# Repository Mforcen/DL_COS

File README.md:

# DL_COS
This project aims to develop a proof of concept of a datalogger with a several tasks operating concurrently in a cooperative way.

Although the name is an acronym for Cooperative Operating System, it is not really an Operating System, since it can't stop the execution of a task.

All the modules are programmed following a state machine structure, with functions that won't block, hence the Cooperative part of the name.

The firmware includes several components. Among them, we can find:

1. A simple stack-based bytecode interpreter. This module is important because it offers two enhancements. In one hand it allows the device to execute programs can be load from flash without reprogram the whole OS. On the other hand, the user does not have to take care about the cooperative behaviour, since the execution of the program is controlled by the module. Finally, this makes the communication quite simple, since a user only needs to call the write function and the OS executes the communications asyncronously, halting the execution of the bytecode program until the communication is finished. This module is intended to use with another piece of software.
2. A SDI12 driver. This manages the communications with several field sensors. This module allows the device to read all the data from the sensors, following the SDI12 specification. This piece of software only needs two timers and a GPIO pin with interruptions enabled. This driver is tested with several SDI12 devices, such as MPS6 sensors-
3. A SPI arbitrer. This makes sure that only one SPI device is in use at once. It is used in the LoRa module and in the SPI Flash module.
4. A logging file system. This allows to write logs to the internal SPI flash memory.
5. A communication driver. This is an effort to write a device communication abstraction model, in order to make an standard API to expose several types of communication devices. It only implements a SIM800L driver in HTTP and SMS mode.

## What this this
This is a Proof of Concept that shows how a datalogger could work, with several modules working concurrently. This is more an academic exercise that gives a glimpse about the integration of several elements working together.
It could be seen also as a reference to implement some modules into your own work.

## What this is not
This is not the best way to make a datalogger. There are several design flaws that I realized when I was developing this project.
For example, writing state machines in C is tedious and makes the code messy and hard to debug. It is true that the code is highly portable, since it allows not to use assembly to make things like coroutines, but the embedded developing is a highly specific activity, so it is worthwhile to do several things in a less portable way.

## License
Copyright 2021 Manuel Forcén Muñoz

Permission is hereby granted, free of charge, to any person obtaining a copy of this software and associated documentation files (the "Software"), to deal in the Software without restriction, including without limitation the rights to use, copy, modify, merge, publish, distribute, sublicense, and/or sell copies of the Software, and to permit persons to whom the Software is furnished to do so, subject to the following conditions:

The above copyright notice and this permission notice shall be included in all copies or substantial portions of the Software.
THE SOFTWARE IS PROVIDED "AS IS", WITHOUT WARRANTY OF ANY KIND, EXPRESS OR IMPLIED, INCLUDING BUT NOT LIMITED TO THE WARRANTIES OF MERCHANTABILITY, FITNESS FOR A PARTICULAR PURPOSE AND NONINFRINGEMENT. IN NO EVENT SHALL THE AUTHORS OR COPYRIGHT HOLDERS BE LIABLE FOR ANY CLAIM, DAMAGES OR OTHER LIABILITY, WHETHER IN AN ACTION OF CONTRACT, TORT OR OTHERWISE, ARISING FROM, OUT OF OR IN CONNECTION WITH THE SOFTWARE OR THE USE OR OTHER DEALINGS IN THE SOFTWARE.

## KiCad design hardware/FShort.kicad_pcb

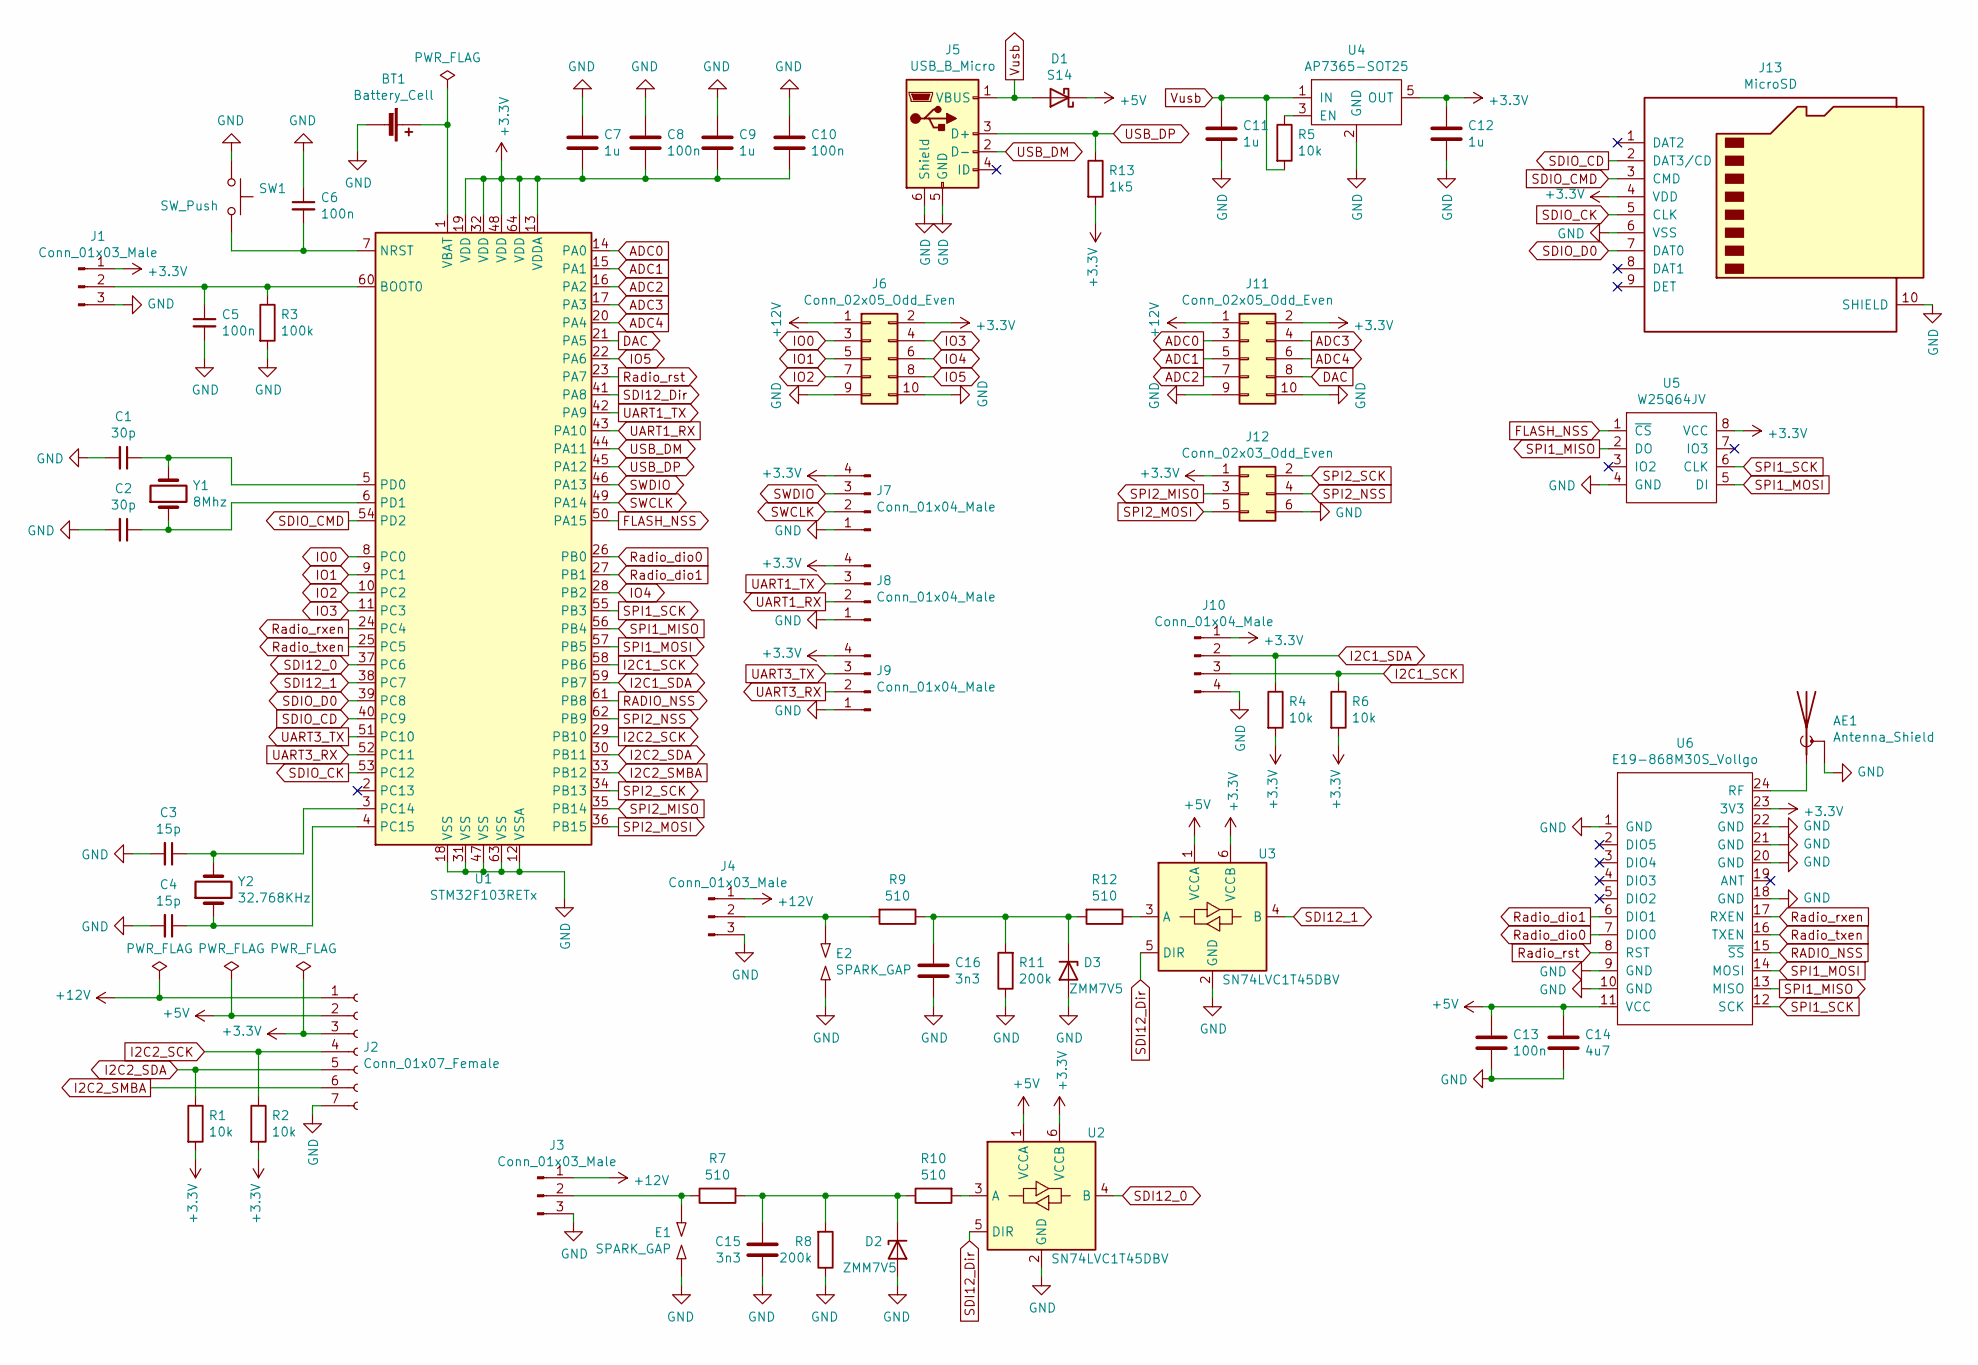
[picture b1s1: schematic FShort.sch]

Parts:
AE1: Antenna_Shield; KH-IPEX3-2020
BT1: Battery_Cell; BT-CR2032
C1, C2: 30p; C_0603_1608Metric
C3, C4: 15p; C_0603_1608Metric
C5, C6, C8, C10, C13: 100n; C_0603_1608Metric
C7, C9, C11, C12: 1u; C_0603_1608Metric
C14: 4u7; C_0603_1608Metric
C15, C16: 3n3; C_0603_1608Metric
D1: S14; D_SMA; LCSCPart C215963
D2, D3: ZMM7V5; D_MiniMELF
E1, E2: SPARK_GAP; SDI12-SparkGap
J1: Conn_01x03_Male; SolderJumper-3_P1.3mm_Open_Pad1.0x1.5mm
J2: Conn_01x07_Female; PinHeader_1x07_P2.54mm_Vertical
J3, J4: Conn_01x03_Male; JST_EH_B3B-EH-A_1x03_P2.50mm_Vertical
J5: USB_B_Micro; USB_Micro-B_Molex-105017-0001
J6, J11: Conn_02x05_Odd_Even; PinHeader_2x05_P2.54mm_Vertical_SMD
J7, J8: Conn_01x04_Male; JST_EH_B4B-EH-A_1x04_P2.50mm_Vertical
J9, J10: Conn_01x04_Male; Conn_SMD_01x04_Wire
J12: Conn_02x03_Odd_Even; PinHeader_2x03_P2.54mm_Vertical_SMD
J13: MicroSD; MicroSD-KoreanHroparts
R1, R2, R4, R5, R6: 10k; R_0603_1608Metric
R3: 100k; R_0603_1608Metric
R7, R9, R10, R12: 510; R_0603_1608Metric
R8, R11: 200k; R_0603_1608Metric
R13: 1k5; R_0603_1608Metric
SW1: SW_Push; Button_SMD_SPST_5.2x5.2mm
U1: STM32F103RETx; LQFP-64_10x10mm_P0.5mm
U2, U3: SN74LVC1T45DBV; SOT-23-6; LCSCPart C441821
U4: AP7365-SOT25; SOT-23-5; LCSCPart C150742
U5: W25Q64JV; SOP-8_5.28x5.23mm_P1.27mm
U6: E19-868M30S_Vollgo; E19-868MS1W_VollGo
Y1: 8Mhz; Crystal_SMD_5032-2Pin_5.0x3.2mm; LCSCPart C390781
Y2: 32.768KHz; Crystal_SMD_1610-2Pin_1.6x1.0mm; LCSCPart C253734

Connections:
+3V3: C7.2, C8.2, C9.2, C10.2, C12.1, J1.1, J2.3, J6.2, J7.4, J8.4, J9.4, J10.1, J11.2, J12.1, J13.4 (VDD), R1.2, R2.2, R4.2, R6.2, R13.2, U1.13 (VDDA), U1.19 (VDD), U1.32 (VDD), U1.48 (VDD), U1.64 (VDD), U2.6 (VCCB), U3.6 (VCCB), U4.5 (OUT), U5.8 (VCC), U6.23 (3V3)
+5V: C13.1, C14.1, D1.1 (K), J2.2, U2.1 (VCCA), U3.1 (VCCA), U6.11 (VCC)
+12V: J2.1, J3.1, J4.1, J6.1, J11.1
ADC0: J11.3, U1.14 (PA0)
ADC1: J11.5, U1.15 (PA1)
ADC2: J11.7, U1.16 (PA2)
ADC3: J11.4, U1.17 (PA3)
ADC4: J11.6, U1.20 (PA4)
DAC: J11.8, U1.21 (PA5)
FLASH_NSS: U1.50 (PA15), U5.1 (~CS)
GND: AE1.2 (Shield), BT1.2 (-), C1.2, C2.2, C3.2, C4.2, C5.2, C6.1, C7.1, C8.1, C9.1, C10.1, C11.2, C12.2, C13.2, C14.2, C15.2, C16.2, D2.2 (A), D3.2 (A), E1.2, E2.2, J1.3, J2.7, J3.3, J4.3, J5.5 (GND), J5.6 (Shield), J6.9, J6.10, J7.1, J8.1, J9.1, J10.4, J11.9, J11.10, J12.6, J13.6 (VSS), J13.10 (SHIELD), R3.2, R8.1, R11.1, SW1.1, U1.12 (VSSA), U1.18 (VSS), U1.31 (VSS), U1.47 (VSS), U1.63 (VSS), U2.2 (GND), U3.2 (GND), U4.2 (GND), U5.4 (GND), U6.1 (GND), U6.9 (GND), U6.10 (GND), U6.18 (GND), U6.20 (GND), U6.21 (GND), U6.22 (GND)
I2C1_SCK: J10.3, R6.1, U1.58 (PB6)
I2C1_SDA: J10.2, R4.1, U1.59 (PB7)
I2C2_SCK: J2.4, R2.1, U1.29 (PB10)
I2C2_SDA: J2.5, R1.1, U1.30 (PB11)
I2C2_SMBA: J2.6, U1.33 (PB12)
IO0: J6.3, U1.8 (PC0)
IO1: J6.5, U1.9 (PC1)
IO2: J6.7, U1.10 (PC2)
IO3: J6.4, U1.11 (PC3)
IO4: J6.6, U1.28 (PB2)
IO5: J6.8, U1.22 (PA6)
unnamed: AE1.1 (A), U6.24 (RF)
unnamed: BT1.1 (+), U1.1 (VBAT)
unnamed: C1.1, U1.5 (PD0), Y1.2
unnamed: C2.1, U1.6 (PD1), Y1.1
unnamed: C3.1, U1.3 (PC14), Y2.2
unnamed: C4.1, U1.4 (PC15), Y2.1
unnamed: C5.1, J1.2, R3.1, U1.60 (BOOT0)
unnamed: C6.2, SW1.2, U1.7 (NRST)
unnamed: C15.1, D2.1 (K), R7.2, R8.2, R10.1
unnamed: C16.1, D3.1 (K), R9.1, R11.2, R12.2
unnamed: E1.1, J3.2, R7.1
unnamed: E2.1, J4.2, R9.2
unnamed: R5.1, U4.3 (EN)
unnamed: R10.2, U2.3 (A)
unnamed: R12.1, U3.3 (A)
RADIO_NSS: U1.61 (PB8), U6.15 (~SS)
Radio_dio0: U1.26 (PB0), U6.7 (DIO0)
Radio_dio1: U1.27 (PB1), U6.6 (DIO1)
Radio_rst: U1.23 (PA7), U6.8 (RST)
Radio_rxen: U1.24 (PC4), U6.17 (RXEN)
Radio_txen: U1.25 (PC5), U6.16 (TXEN)
SDI12_0: U1.37 (PC6), U2.4 (B)
SDI12_1: U1.38 (PC7), U3.4 (B)
SDI12_Dir: U1.41 (PA8), U2.5 (DIR), U3.5 (DIR)
SDIO_CD: J13.2 (DAT3/CD), U1.40 (PC9)
SDIO_CK: J13.5 (CLK), U1.53 (PC12)
SDIO_CMD: J13.3 (CMD), U1.54 (PD2)
SDIO_D0: J13.7 (DAT0), U1.39 (PC8)
SPI1_MISO: U1.56 (PB4), U5.2 (DO), U6.13 (MISO)
SPI1_MOSI: U1.57 (PB5), U5.5 (DI), U6.14 (MOSI)
SPI1_SCK: U1.55 (PB3), U5.6 (CLK), U6.12 (SCK)
SPI2_MISO: J12.3, U1.35 (PB14)
SPI2_MOSI: J12.5, U1.36 (PB15)
SPI2_NSS: J12.4, U1.62 (PB9)
SPI2_SCK: J12.2, U1.34 (PB13)
SWCLK: J7.2, U1.49 (PA14)
SWDIO: J7.3, U1.46 (PA13)
UART1_RX: J8.2, U1.43 (PA10)
UART1_TX: J8.3, U1.42 (PA9)
UART3_RX: J9.2, U1.52 (PC11)
UART3_TX: J9.3, U1.51 (PC10)
USB_DM: J5.2 (D-), U1.44 (PA11)
USB_DP: J5.3 (D+), R13.1, U1.45 (PA12)
Vusb: C11.1, D1.2 (A), J5.1 (VBUS), R5.2, U4.1 (IN)

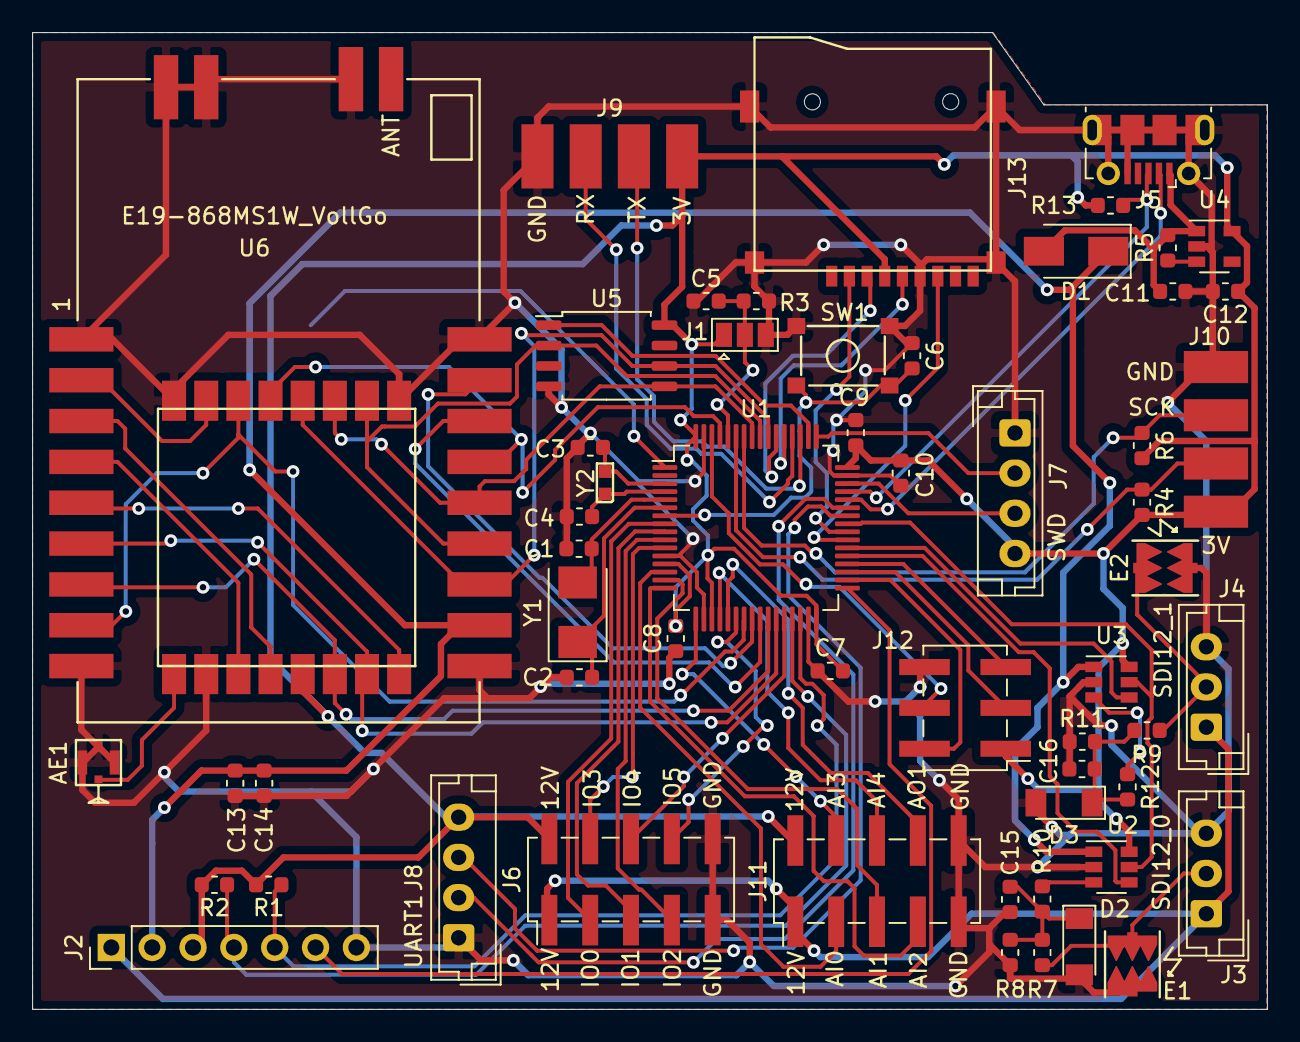
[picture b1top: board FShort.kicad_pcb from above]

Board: 2 copper layers, 76.8 x 60.8 mm, 58 parts (1 on the bottom side), 66 nets.

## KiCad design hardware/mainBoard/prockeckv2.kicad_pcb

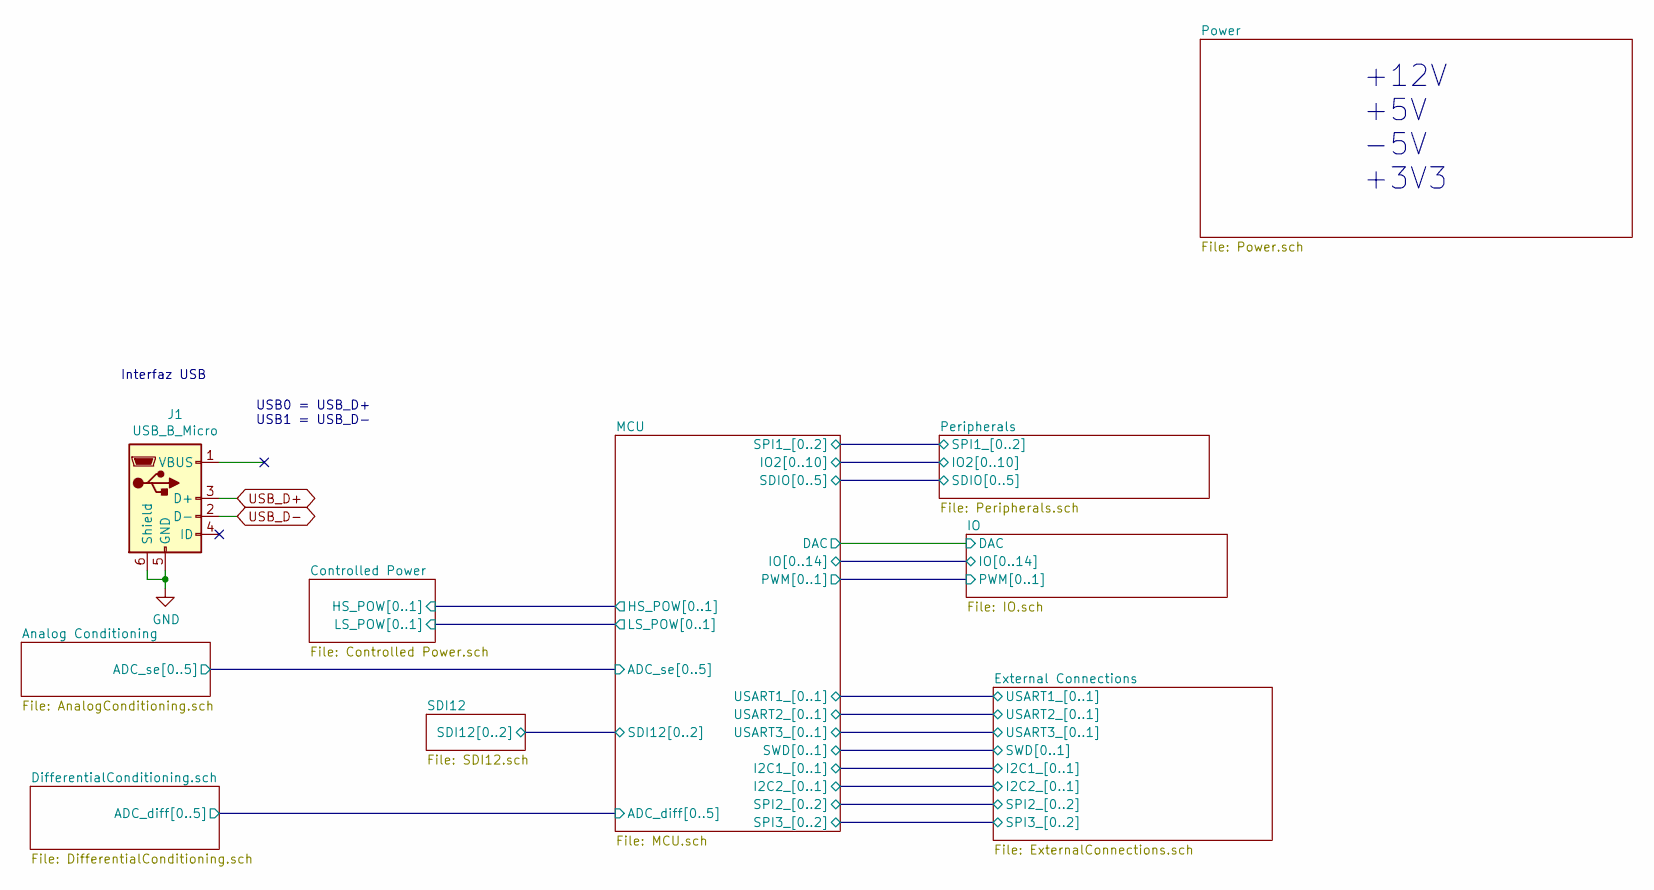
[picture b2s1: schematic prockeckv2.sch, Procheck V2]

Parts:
J1: USB_B_Micro; USB_Micro-B_Molex-105017-0001

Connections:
GND: J1.5 (GND), J1.6 (Shield); also elsewhere on the board
USB_D+: J1.3 (D+); also elsewhere on the board
USB_D-: J1.2 (D-); also elsewhere on the board

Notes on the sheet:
Interfaz USB
+12V +5V -5V +3V3
USB0 = USB_D+ USB1 = USB_D-

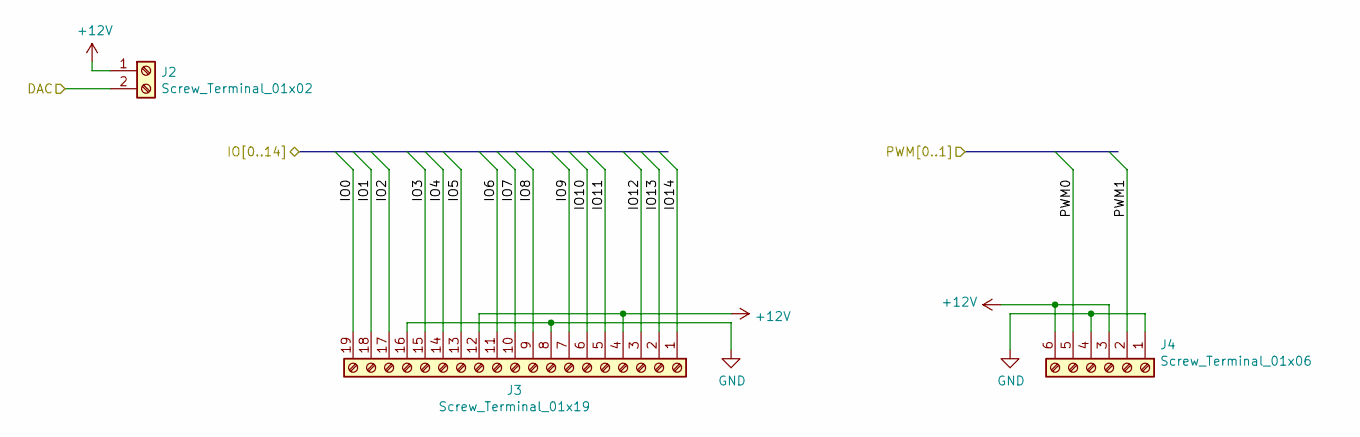
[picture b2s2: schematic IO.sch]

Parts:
J2: Screw_Terminal_01x02; PinHeader_1x02_P2.54mm_Vertical
J3: Screw_Terminal_01x19; TerminalBlock_19_P5.08mm
J4: Screw_Terminal_01x06; PinHeader_1x06_P2.54mm_Vertical

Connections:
+12V: J2.1, J3.4, J3.12, J4.3, J4.6; also elsewhere on the board
/IO/DAC: J2.2; also elsewhere on the board
/IO/IO0: J3.19; also elsewhere on the board
/IO/IO1: J3.18; also elsewhere on the board
/IO/IO2: J3.17; also elsewhere on the board
/IO/IO3: J3.15; also elsewhere on the board
/IO/IO4: J3.14; also elsewhere on the board
/IO/IO5: J3.13; also elsewhere on the board
/IO/IO6: J3.11; also elsewhere on the board
/IO/IO7: J3.10; also elsewhere on the board
/IO/IO8: J3.9; also elsewhere on the board
/IO/IO9: J3.7; also elsewhere on the board
/IO/IO10: J3.6; also elsewhere on the board
/IO/IO11: J3.5; also elsewhere on the board
/IO/IO12: J3.3; also elsewhere on the board
/IO/IO13: J3.2; also elsewhere on the board
/IO/IO14: J3.1; also elsewhere on the board
/MCU/PWM0: J4.5; also elsewhere on the board
/MCU/PWM1: J4.2; also elsewhere on the board
GND: J3.8, J3.16, J4.1, J4.4; also elsewhere on the board

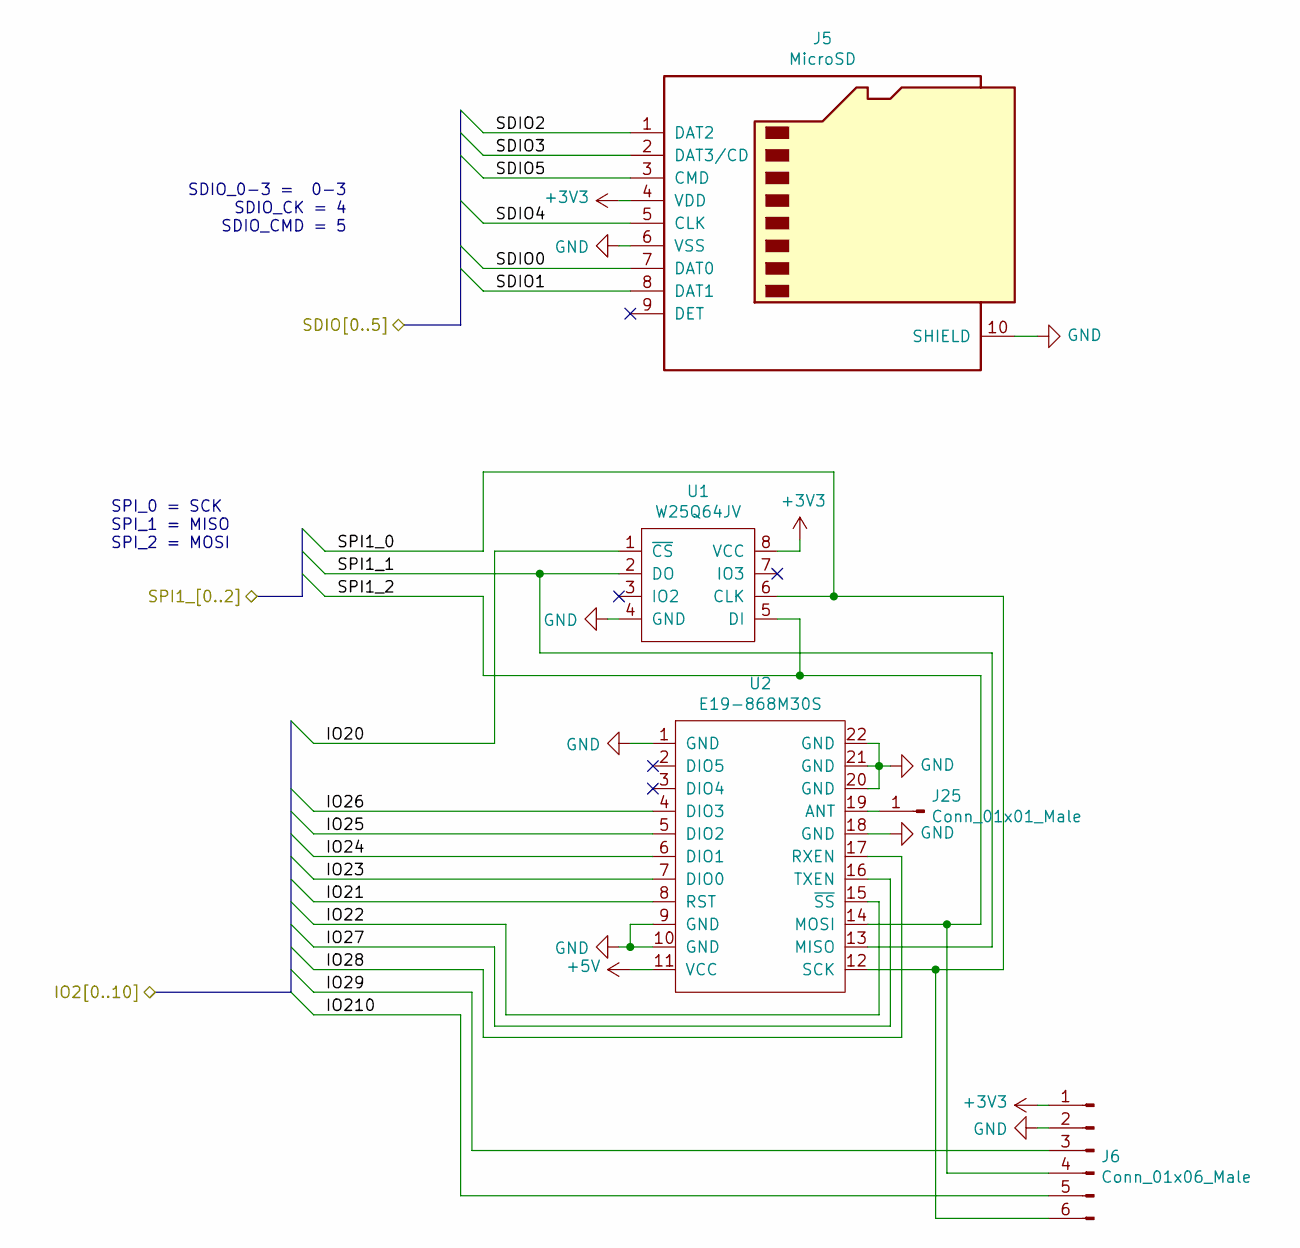
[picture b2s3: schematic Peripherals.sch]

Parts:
J5: MicroSD; MicroSD-KoreanHroparts
J6: Conn_01x06_Male; JST_XH_B6B-XH-A_1x06_P2.50mm_Vertical
J25: Conn_01x01_Male; SolderWirePad_1x01_SMD_5x10mm
U1: W25Q64JV; SOIC-8_5.23x5.23mm_P1.27mm
U2: E19-868M30S; E19-868MS1W

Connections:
+5V: U2.11 (VCC); also elsewhere on the board
/MCU/IO20: U1.1 (~CS); also elsewhere on the board
/MCU/IO21: U2.8 (RST); also elsewhere on the board
/MCU/IO22: U2.15 (~SS); also elsewhere on the board
/MCU/IO23: U2.7 (DIO0); also elsewhere on the board
/MCU/IO24: U2.6 (DIO1); also elsewhere on the board
/MCU/IO25: U2.5 (DIO2); also elsewhere on the board
/MCU/IO26: U2.4 (DIO3); also elsewhere on the board
/MCU/IO27: U2.16 (TXEN); also elsewhere on the board
/MCU/IO28: U2.17 (RXEN); also elsewhere on the board
/MCU/IO29: J6.3; also elsewhere on the board
/MCU/IO210: J6.5; also elsewhere on the board
/MCU/SDIO0: J5.7 (DAT0); also elsewhere on the board
/MCU/SDIO1: J5.8 (DAT1); also elsewhere on the board
/MCU/SDIO2: J5.1 (DAT2); also elsewhere on the board
/MCU/SDIO3: J5.2 (DAT3/CD); also elsewhere on the board
/MCU/SDIO4: J5.5 (CLK); also elsewhere on the board
/MCU/SDIO5: J5.3 (CMD); also elsewhere on the board
/MCU/SPI1_0: J6.6, U1.6 (CLK), U2.12 (SCK); also elsewhere on the board
/MCU/SPI1_1: U1.2 (DO), U2.13 (MISO); also elsewhere on the board
/MCU/SPI1_2: J6.4, U1.5 (DI), U2.14 (MOSI); also elsewhere on the board
GND: J5.6 (VSS), J5.10 (SHIELD), J6.2, U1.4 (GND), U2.1 (GND), U2.9 (GND), U2.10 (GND), U2.18 (GND), U2.20 (GND), U2.21 (GND), U2.22 (GND); also elsewhere on the board
unnamed: J25.1, U2.19 (ANT)

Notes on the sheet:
SPI_0 = SCK SPI_1 = MISO SPI_2 = MOSI
SDIO_0-3 = 0-3 SDIO_CK = 4 SDIO_CMD = 5

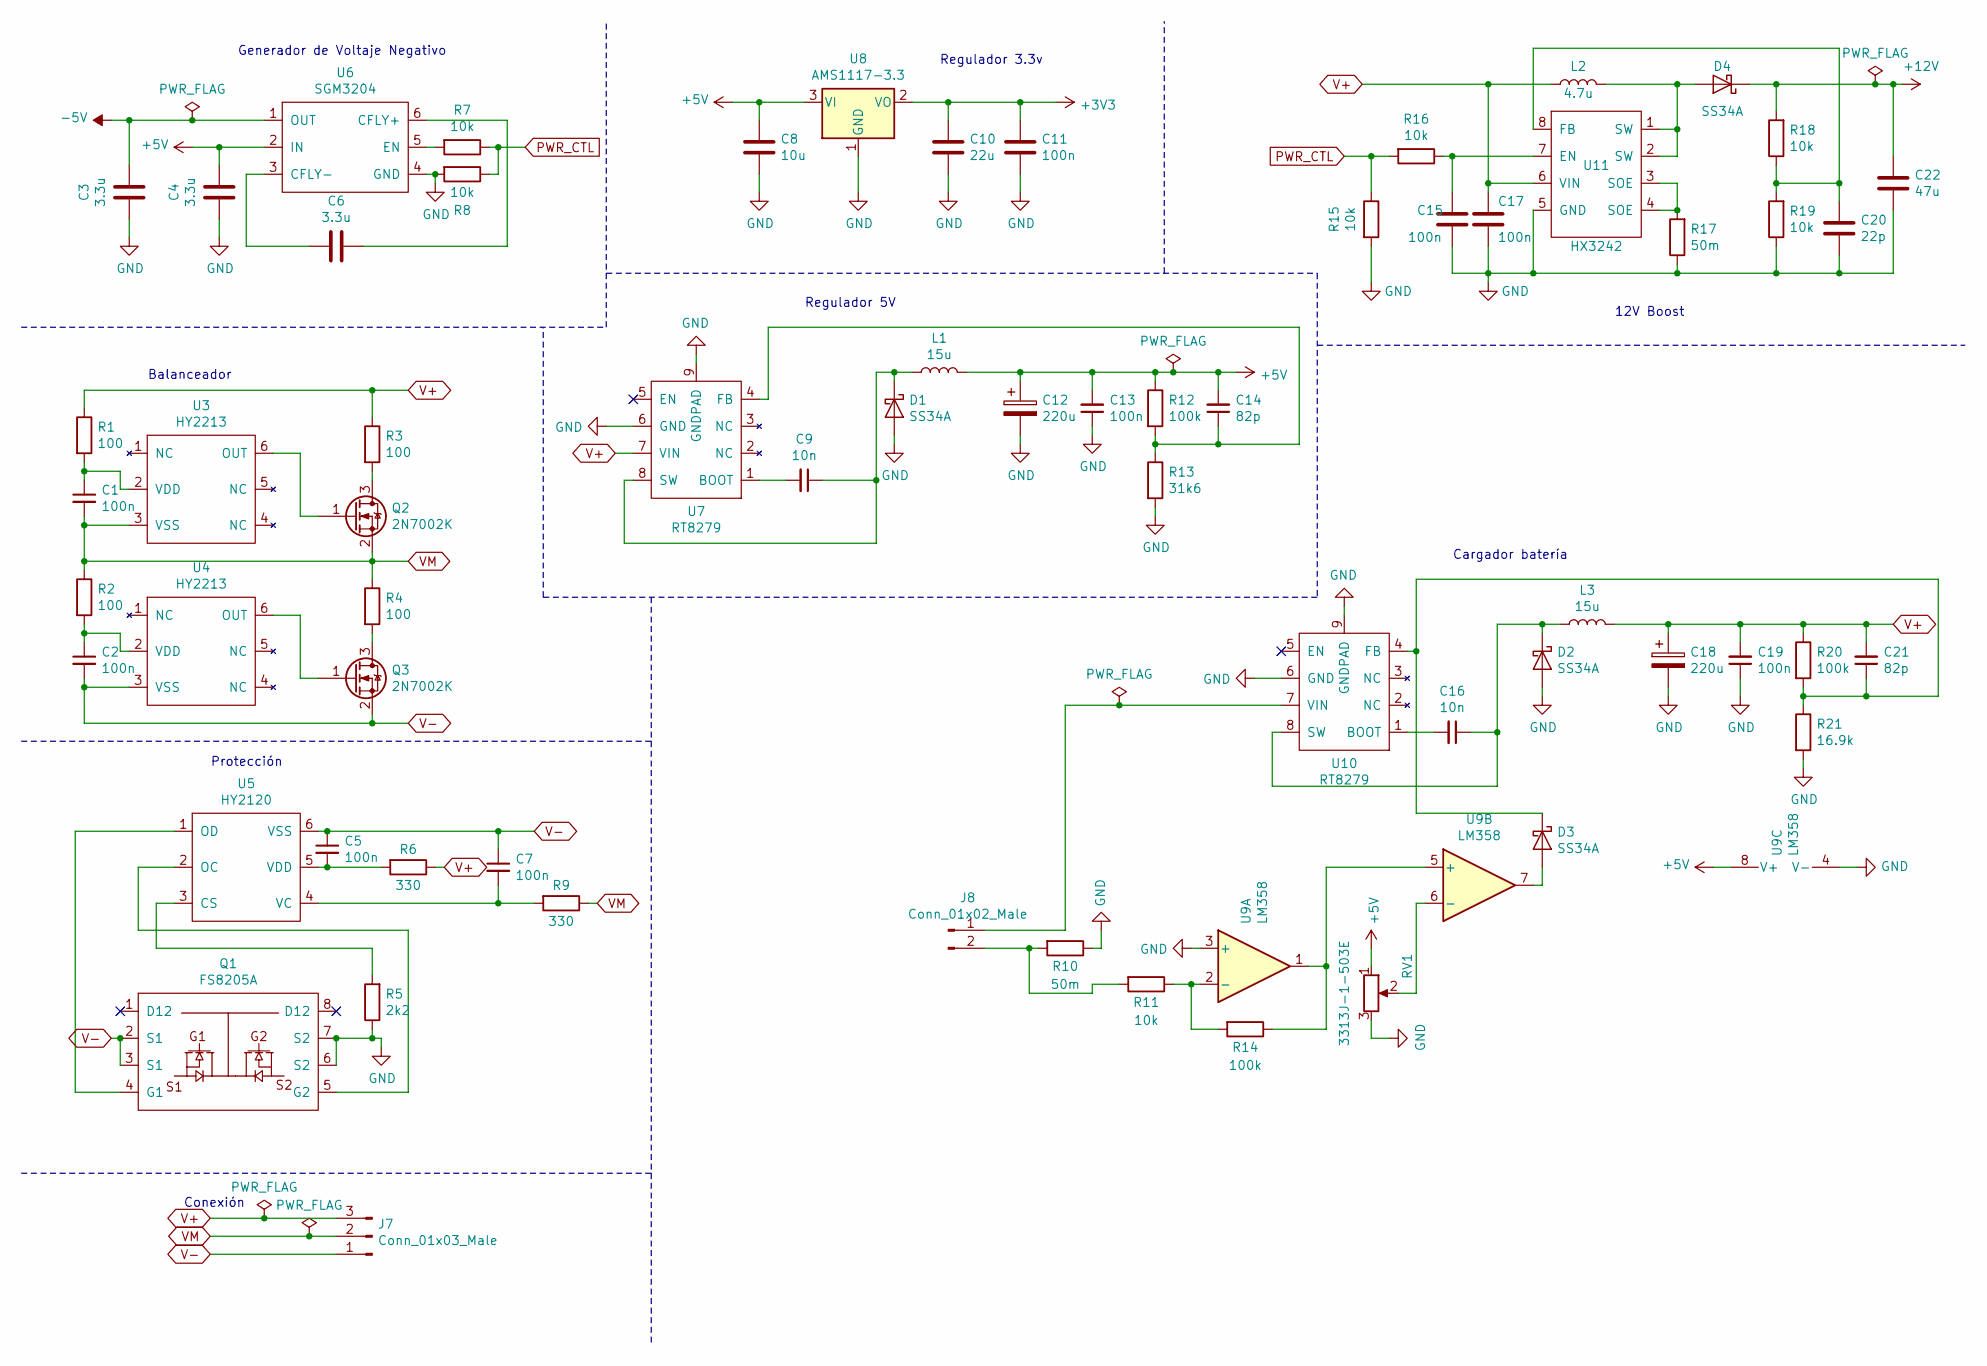
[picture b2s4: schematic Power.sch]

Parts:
C1, C2, C5, C7, C11, C13, C15, C17, C19: 100n; C_0603_1608Metric_Pad1.05x0.95mm_HandSolder
C3, C4, C6: 3.3u; C_0603_1608Metric_Pad1.05x0.95mm_HandSolder
C8: 10u; C_0603_1608Metric_Pad1.05x0.95mm_HandSolder
C9, C16: 10n; C_0603_1608Metric_Pad1.05x0.95mm_HandSolder
C10: 22u; C_0603_1608Metric_Pad1.05x0.95mm_HandSolder
C12, C18: 220u; CP_Elec_6.3x5.4
C14, C21: 82p; C_0603_1608Metric_Pad1.05x0.95mm_HandSolder
C20: 22p; C_0603_1608Metric_Pad1.05x0.95mm_HandSolder
C22: 47u; C_1206_3216Metric_Pad1.42x1.75mm_HandSolder
D1, D2, D3, D4: SS34A; D_SMA
J7: Conn_01x03_Male; JST_EH_B3B-EH-A_1x03_P2.50mm_Vertical
J8: Conn_01x02_Male; JST_EH_B2B-EH-A_1x02_P2.50mm_Vertical
L1: 15u; SLO0630h; MPN SLO0630H150MTT
L2: 4.7u; L_Taiyo-Yuden_NR-60xx_HandSoldering
L3: 15u; SLO0630h
Q1: FS8205A; TSSOP-8_4.4x3mm_P0.65mm
Q2, Q3: 2N7002K; SOT-23_Handsoldering
R1, R2, R3, R4: 100; R_0603_1608Metric_Pad1.05x0.95mm_HandSolder
R5: 2k2; R_0603_1608Metric_Pad1.05x0.95mm_HandSolder
R6, R9: 330; R_0603_1608Metric_Pad1.05x0.95mm_HandSolder
R7, R8, R11, R15, R16, R18, R19: 10k; R_0603_1608Metric_Pad1.05x0.95mm_HandSolder
R10, R17: 50m; R_0603_1608Metric_Pad1.05x0.95mm_HandSolder
R12, R14, R20: 100k; R_0603_1608Metric_Pad1.05x0.95mm_HandSolder
R13: 31k6; R_0603_1608Metric_Pad1.05x0.95mm_HandSolder
R21: 16.9k; R_0603_1608Metric_Pad1.05x0.95mm_HandSolder
RV1: 3313J-1-503E; Bourns 3313J
U3: HY2213; SOT-23-6_Handsoldering
U4: HY2213; SOT-23-6_Handsoldering; MPN HY2213-BB3A
U5: HY2120; SOT-23-6_Handsoldering
U6: SGM3204; SOT-23-6_Handsoldering
U7, U10: RT8279; SOIC-8-1EP_3.9x4.9mm_P1.27mm_EP2.514x3.2mm_ThermalVias
U8: AMS1117-3.3; SOT-223-3_TabPin2
U9: LM358; SOIC-8_3.9x4.9mm_P1.27mm
U11: HX3242; SOIC-8_3.9x4.9mm_P1.27mm

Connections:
+5V: C4.2, C8.1, C12.1, C13.2, C14.2, L1.2, R12.1, RV1.1, U6.2 (IN), U8.3 (VI), U9.8 (V+); also elsewhere on the board
+12V: C22.1, D4.1 (K), R18.2; also elsewhere on the board
-5V: C3.2, U6.1 (OUT); also elsewhere on the board
GND: C3.1, C4.1, C8.2, C10.2, C11.2, C12.2, C13.1, C15.2, C17.2, C18.2, C19.1, C20.2, C22.2, D1.2 (A), D2.2 (A), Q1.6 (S2), Q1.7 (S2), R5.1, R8.2, R10.1, R13.2, R15.2, R17.1, R19.1, R21.2, RV1.3, U6.4 (GND), U7.6 (GND), U7.9 (GNDPAD), U8.1 (GND), U9.3 (+), U9.4 (V-), U10.6 (GND), U10.9 (GNDPAD), U11.5 (GND); also elsewhere on the board
unnamed: C1.1, R1.2, U3.2 (VDD)
unnamed: C2.1, R2.2, U4.2 (VDD)
unnamed: C5.2, R6.2, U5.5 (VDD)
unnamed: C6.1, U6.3 (CFLY-)
unnamed: C6.2, U6.6 (CFLY+)
unnamed: C7.2, R9.2, U5.4 (VC)
unnamed: C9.1, D1.1 (K), L1.1, U7.8 (SW)
unnamed: C9.2, U7.1 (BOOT)
unnamed: C14.1, R12.2, R13.1, U7.4 (FB)
unnamed: C15.1, R16.1, U11.7 (EN)
unnamed: C16.1, D2.1 (K), L3.1, U10.8 (SW)
unnamed: C16.2, U10.1 (BOOT)
unnamed: C20.1, R18.1, R19.2, U11.8 (FB)
unnamed: C21.1, D3.1 (K), R20.2, R21.1, U10.4 (FB)
unnamed: D3.2 (A), U9.7
unnamed: D4.2 (A), L2.2, U11.1 (SW), U11.2 (SW)
unnamed: J8.1, U10.7 (VIN)
unnamed: J8.2, R10.2, R11.2
unnamed: Q1.4 (G1), U5.1 (OD)
unnamed: Q1.5 (G2), U5.2 (OC)
unnamed: Q2.1 (G), U3.6 (OUT)
unnamed: Q2.3 (D), R3.2
unnamed: Q3.1 (G), U4.6 (OUT)
unnamed: Q3.3 (D), R4.2
unnamed: R5.2, U5.3 (CS)
unnamed: R7.2, U6.5 (EN)
unnamed: R11.1, R14.2, U9.2 (-)
unnamed: R14.1, U9.1, U9.5 (+)
unnamed: R17.2, U11.3 (SOE), U11.4 (SOE)
unnamed: RV1.2, U9.6 (-)
PWR_CTL: R7.1, R8.1, R15.1, R16.2; also elsewhere on the board
V+: C17.1, C18.1, C19.2, C21.2, J7.3, L2.1, L3.2, R1.1, R3.1, R6.1, R20.1, U7.7 (VIN), U11.6 (VIN)
V-: C2.2, C5.1, C7.1, J7.1, Q1.2 (S1), Q1.3 (S1), Q3.2 (S), U4.3 (VSS), U5.6 (VSS)
VM: C1.2, J7.2, Q2.2 (S), R2.1, R4.1, R9.1, U3.3 (VSS)

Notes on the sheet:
Generador de Voltaje Negativo
Regulador 3.3v
12V Boost
Balanceador
Protección
Conexión
Regulador 5V
Cargador batería
